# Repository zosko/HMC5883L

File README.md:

# HMC5883L-module
HMC5883L Module board

## Scheme

## Board

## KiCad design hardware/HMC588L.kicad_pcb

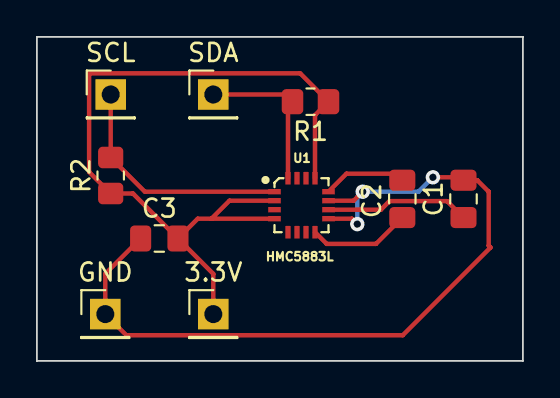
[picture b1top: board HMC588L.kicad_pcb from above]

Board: 2 copper layers, 27.0 x 18.0 mm, 10 parts (0 on the bottom side), 7 nets.

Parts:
3.3V: 3.3V; PinHeader_1x01_P2.54mm_Vertical
C1: 4.7uF; C_0805_2012Metric_Pad1.18x1.45mm_HandSolder
C2: 220nF; C_0805_2012Metric_Pad1.18x1.45mm_HandSolder
C3: 100nF; C_0805_2012Metric_Pad1.18x1.45mm_HandSolder
GND: GND; PinHeader_1x01_P2.54mm_Vertical
R1, R2: 4.7K; R_0805_2012Metric_Pad1.20x1.40mm_HandSolder
SCL: SCL; PinHeader_1x01_P2.54mm_Vertical
SDA: SDA; PinHeader_1x01_P2.54mm_Vertical
U1: HMC5883L; PLCC16-0.5-3X3MM

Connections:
3.3V: 3.3V.1, C3.2, R1.1, R2.1, U1.2 (2(VDD)), U1.4 (4(S1)), U1.13 (13(VDDIO))
GND: C1.2, C3.1, GND.1, U1.9 (9(GND)), U1.11 (11(GND))
unnamed: C2.2, U1.8 (8(SETP))
unnamed: C1.1, U1.10 (10(C1))
unnamed: C2.1, U1.12 (12(SETC))
SCL: R2.2, SCL.1, U1.1 (1(SCL))
SDA: R1.2, SDA.1, U1.16 (16(SDA))
